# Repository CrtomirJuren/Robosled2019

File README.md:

# Robosled2019
delavnica robosled. kicad arduino itd

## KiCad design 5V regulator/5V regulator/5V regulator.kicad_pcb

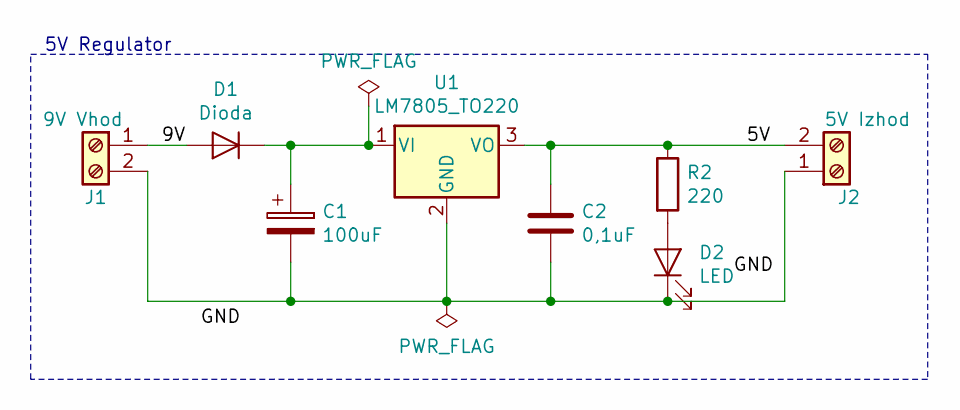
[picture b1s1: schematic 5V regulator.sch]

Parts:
C1: 100uF; CP_Radial_D8.0mm_P3.50mm
C2: 0,1uF; C_Disc_D10.0mm_W2.5mm_P5.00mm
D1: Dioda; D_DO-41_SOD81_P10.16mm_Horizontal
D2: LED; LED_D3.0mm
J1: 9V Vhod; TerminalBlock_bornier-2_P5.08mm
J2: 5V Izhod; TerminalBlock_bornier-2_P5.08mm
R2: 220; R_Axial_DIN0207_L6.3mm_D2.5mm_P10.16mm_Horizontal
U1: LM7805_TO220; TO-220-3_Vertical

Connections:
/5V: C2.1, J2.2, R2.1, U1.3 (VO)
/9V: D1.2 (A), J1.1
unnamed: C1.1, D1.1 (K), U1.1 (VI)
unnamed: C1.2, C2.2, D2.1 (K), J1.2, J2.1, U1.2 (GND)
unnamed: D2.2 (A), R2.2

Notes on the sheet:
5V Regulator

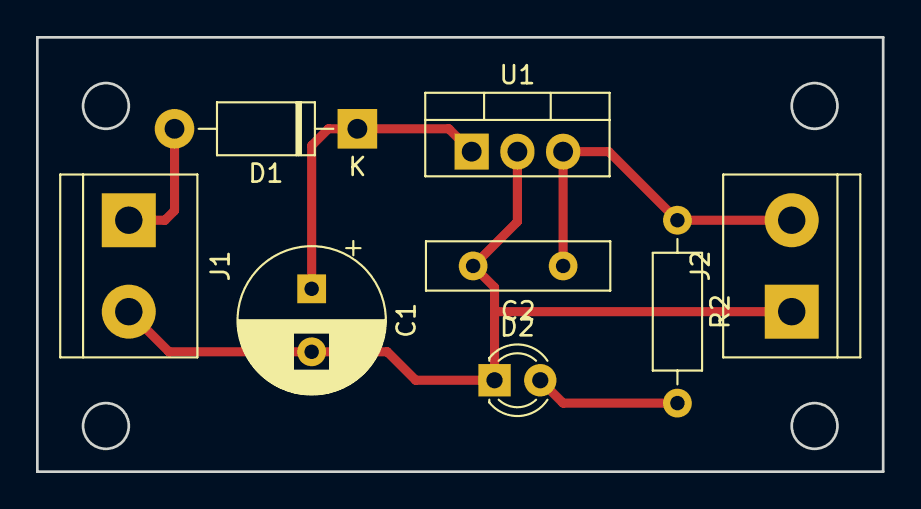
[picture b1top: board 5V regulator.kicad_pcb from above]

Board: 2 copper layers, 47.0 x 24.1 mm, 8 parts (0 on the bottom side), 5 nets.

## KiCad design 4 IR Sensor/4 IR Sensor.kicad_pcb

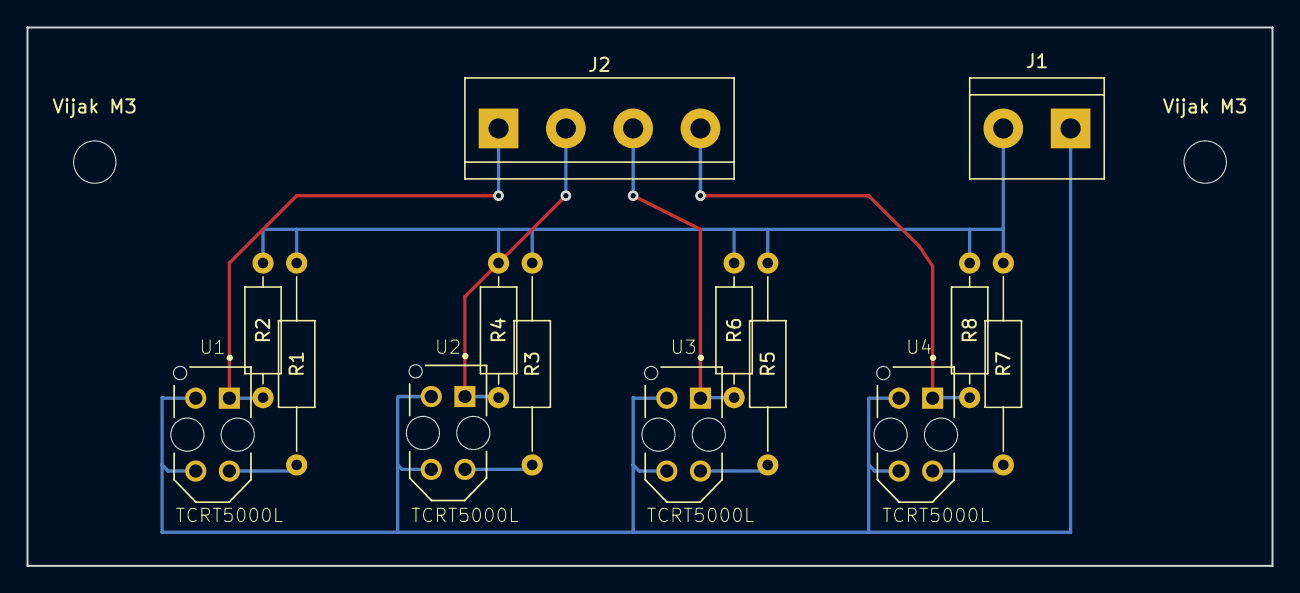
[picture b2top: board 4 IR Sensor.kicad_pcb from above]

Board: 2 copper layers, 94.0 x 40.6 mm, 16 parts (0 on the bottom side), 10 nets.

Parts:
J1: Screw_Terminal_01x02; TerminalBlock_bornier-2_P5.08mm
J2: Screw_Terminal_01x04; TerminalBlock_bornier-4_P5.08mm
R1, R3, R5, R7: 300; R_Axial_DIN0207_L6.3mm_D2.5mm_P15.24mm_Horizontal
R2, R4, R6, R8: 10k; R_Axial_DIN0207_L6.3mm_D2.5mm_P10.16mm_Horizontal
U1, U2, U3, U4: TCRT5000L; XDCR_TCRT5000L
Vijak M3, Vijak M3#2: MountingHole_3.2mm_M3

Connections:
unnamed: J1.1, U1.2, U1.3, U2.2, U2.3, U3.2, U3.3, U4.2, U4.3
unnamed: J1.2, R1.1, R2.2, R3.1, R4.2, R5.1, R6.2, R7.1, R8.2
unnamed: J2.1, R2.1, U1.1
unnamed: J2.2, R4.1, U2.1
unnamed: J2.3, R6.1, U3.1
unnamed: J2.4, R8.1, U4.1
unnamed: R1.2, U1.4
unnamed: R3.2, U2.4
unnamed: R5.2, U3.4
unnamed: R7.2, U4.4

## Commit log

2019-11-17 kicad datoteke dodane
2019-11-17 updated modul 4 ir comparator
